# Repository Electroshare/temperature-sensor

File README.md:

# temperature-sensor
A temperature sensor run on battery,
which sends its data over a nRF24L01 chip.

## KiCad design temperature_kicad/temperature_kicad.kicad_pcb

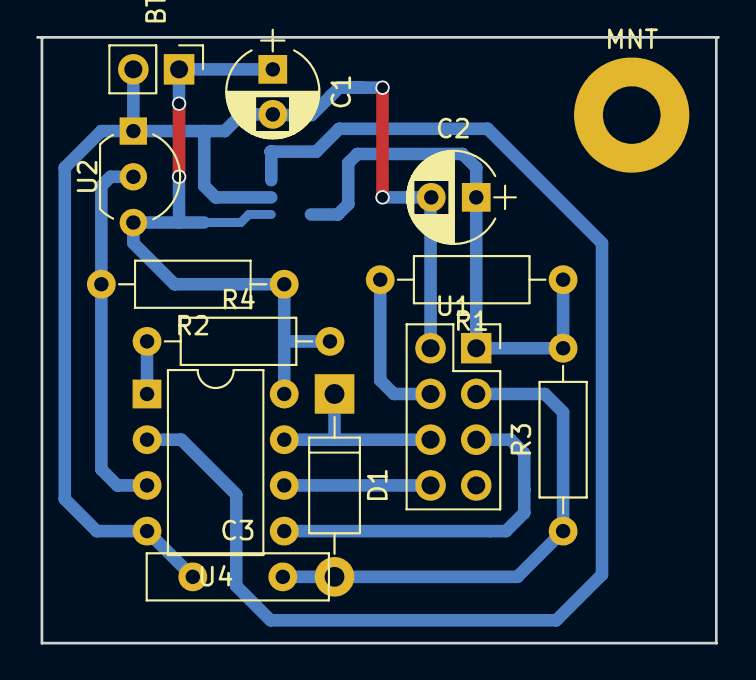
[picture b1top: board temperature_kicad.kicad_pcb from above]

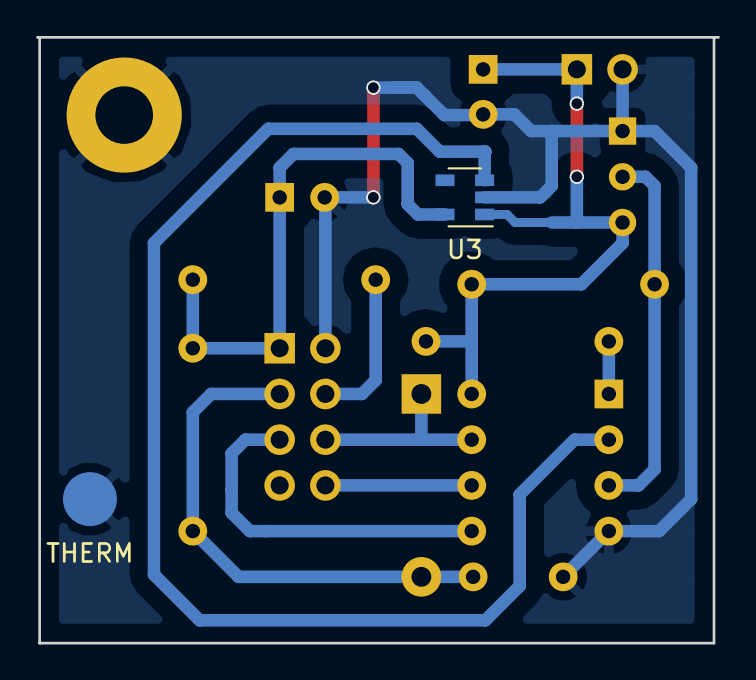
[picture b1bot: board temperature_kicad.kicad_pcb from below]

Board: 2 copper layers, 37.8 x 33.7 mm, 15 parts (2 on the bottom side), 11 nets.

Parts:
BT1: Battery_Cell; Socket_Strip_Straight_1x02_Pitch2.54mm
C1: 1µF; CP_Radial_D5.0mm_P2.50mm
C2: 2.2µF; CP_Radial_D5.0mm_P2.50mm
C3: 0.1µF; C_Disc_D10.0mm_W2.5mm_P5.00mm
D1: D; D_DO-41_SOD81_P10.16mm_Horizontal
MNT: MountingHole_3.2mm_M3_Pad
R1, R3: 1k; R_Axial_DIN0207_L6.3mm_D2.5mm_P10.16mm_Horizontal
R2: 4.7k; R_Axial_DIN0207_L6.3mm_D2.5mm_P10.16mm_Horizontal
R4: 10k; R_Axial_DIN0207_L6.3mm_D2.5mm_P10.16mm_Horizontal
THERM: Measurement_Point_Round-SMD-Pad_Big
U1: nRF24L01; Socket_Strip_Straight_2x04_Pitch2.54mm
U2: DS18B20; TO-92_Inline_Wide
U3: LD2980; SOT-23-5
U4: ATTINY13A-PU; DIP-8_W7.62mm

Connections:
GND: BT1.2, C1.2, C2.2, C3.1, MNT.1, THERM.1, U1.2, U2.1, U3.2, U4.4
unnamed: C3.2, D1.2, R3.1, U1.3
unnamed: D1.1, U1.6, U4.7
unnamed: R1.2, U1.4
unnamed: R2.2, U2.2, U4.3
unnamed: R4.1, U4.1
unnamed: U1.5, U4.5
unnamed: U1.8, U4.6
TR_EN: U3.3, U4.2
VCC: BT1.1, C1.1, R2.1, R4.2, U2.3, U3.1, U4.8
VDD: C2.1, R1.1, R3.2, U1.1, U3.5

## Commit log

2018-06-20 Added first PCB design
2018-06-20 Mention nRF24L01 module in readme
2018-06-21 Redone routing
2018-06-22 pcb route
2018-06-24 code
2018-07-09 Added licence notice to the code
2018-08-03 code with nrf24l01 attiny v1
2018-08-03 update readMe code
2018-08-03 code for main station v1
2018-08-03 code for main station v1.1 + readme
2018-11-03 correct use of csn pin on nrf24l01
2018-11-03 first not-working version
2019-04-07 add simavr target to help debugging
2019-04-07 updated readme for simavr target
